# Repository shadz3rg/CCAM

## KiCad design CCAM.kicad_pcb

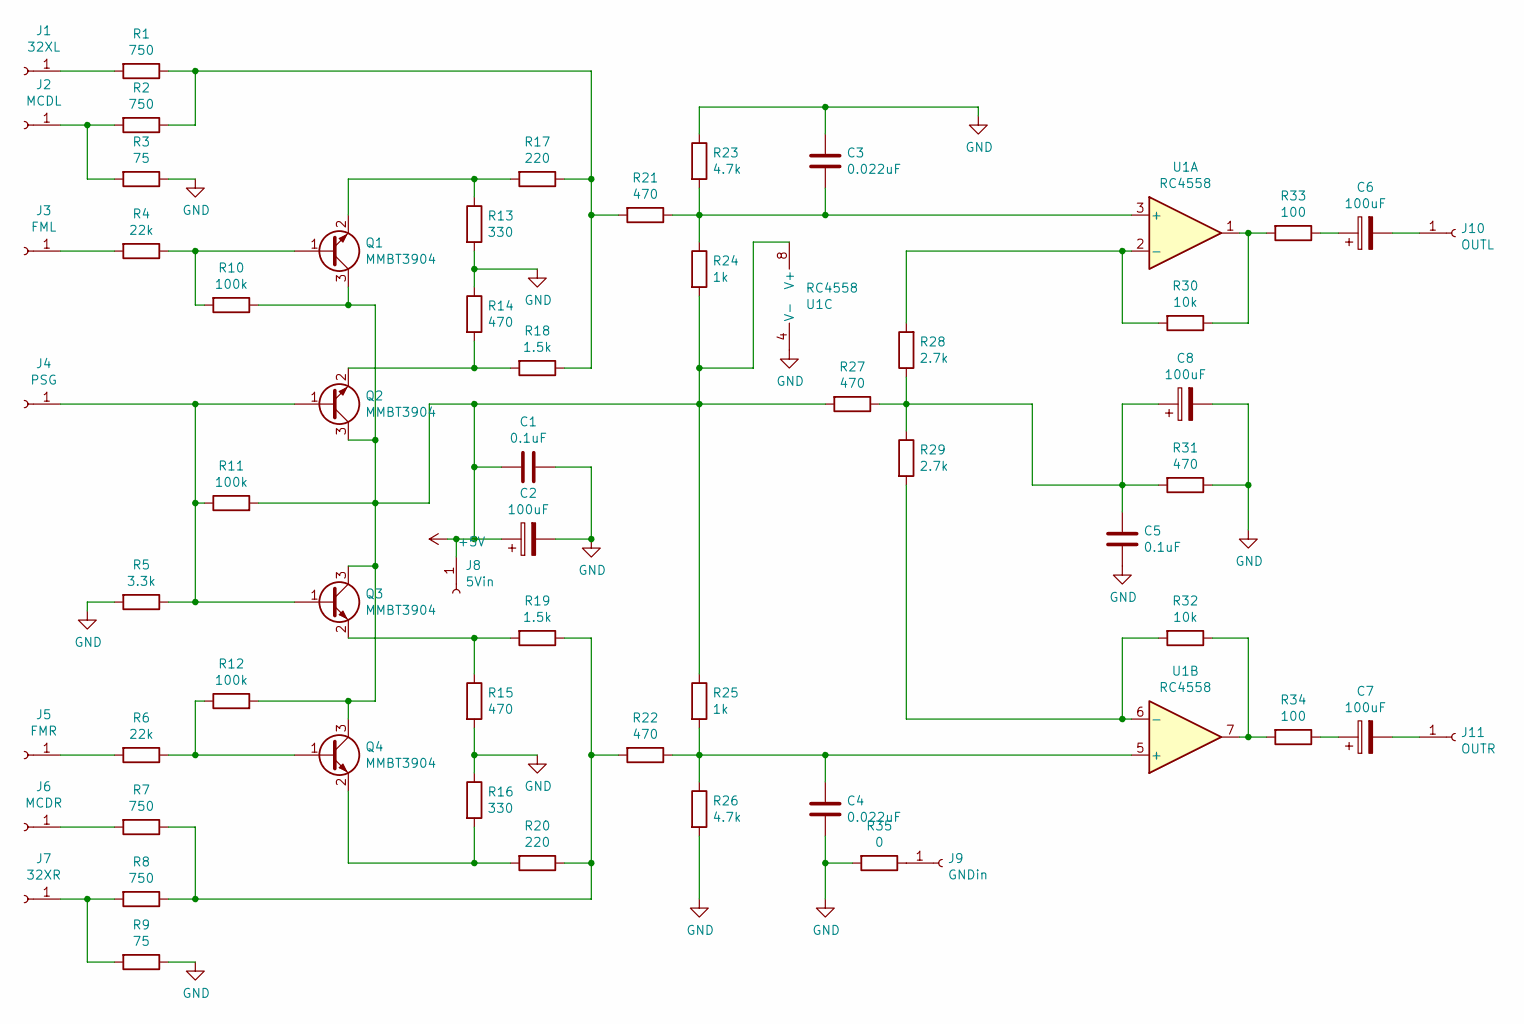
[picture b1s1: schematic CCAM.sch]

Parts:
C1, C5: 0.1uF; C_1210_3225Metric
C2, C6, C7, C8: 100uF; CP_EIA-3528-12_Kemet-T
C3, C4: 0.022uF; C_1210_3225Metric
J1: 32XL; SolderWirePad_1x01_SMD_1x2mm
J2: MCDL; SolderWirePad_1x01_SMD_1x2mm
J3: FML; SolderWirePad_1x01_SMD_1x2mm
J4: PSG; SolderWirePad_1x01_SMD_1x2mm
J5: FMR; SolderWirePad_1x01_SMD_1x2mm
J6: MCDR; SolderWirePad_1x01_SMD_1x2mm
J7: 32XR; SolderWirePad_1x01_SMD_1x2mm
J8: 5Vin; SolderWirePad_1x01_SMD_1x2mm
J9: GNDin; SolderWirePad_1x01_SMD_1x2mm
J10: OUTL; SolderWirePad_1x01_SMD_1x2mm
J11: OUTR; SolderWirePad_1x01_SMD_1x2mm
Q1, Q2, Q3, Q4: MMBT3904; SOT-23
R1, R2, R7, R8: 750; R_1206_3216Metric
R3, R9: 75; R_1206_3216Metric
R4, R6: 22k; R_1206_3216Metric
R5: 3.3k; R_1206_3216Metric
R10, R11, R12: 100k; R_1206_3216Metric
R13, R16: 330; R_1206_3216Metric
R14, R15, R21, R22, R27, R31: 470; R_1206_3216Metric
R17, R20: 220; R_1206_3216Metric
R18, R19: 1.5k; R_1206_3216Metric
R23, R26: 4.7k; R_1206_3216Metric
R24, R25: 1k; R_1206_3216Metric
R28, R29: 2.7k; R_1206_3216Metric
R30, R32: 10k; R_1206_3216Metric
R33, R34: 100; R_1206_3216Metric
R35: 0; R_1206_3216Metric
U1: RC4558; SOIC-8_3.9x4.9mm_P1.27mm

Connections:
+5V: C1.2, C2.1, J8.1, Q1.3 (C), Q2.3 (C), Q3.3 (C), Q4.3 (C), R10.1, R11.2, R12.2, R24.2, R25.1, R27.2, U1.8 (V+)
GND: C1.1, C2.2, C3.1, C4.2, C5.2, C8.2, R3.1, R5.2, R9.1, R13.2, R14.1, R15.2, R16.1, R23.1, R26.2, R31.1, R35.2, U1.4 (V-)
unnamed: C3.2, R21.1, R23.2, R24.1, U1.3 (+)
unnamed: C4.1, R22.1, R25.2, R26.1, U1.5 (+)
unnamed: C5.1, C8.1, R27.1, R28.1, R29.1, R31.2
unnamed: C6.1, R33.1
unnamed: C6.2, J10.1
unnamed: C7.1, R34.1
unnamed: C7.2, J11.1
unnamed: J1.1, R1.2
unnamed: J2.1, R2.2, R3.2
unnamed: J3.1, R4.2
unnamed: J4.1, Q2.1 (B), Q3.1 (B), R5.1, R11.1
unnamed: J5.1, R6.2
unnamed: J6.1, R7.2
unnamed: J7.1, R8.2, R9.2
unnamed: J9.1, R35.1
unnamed: Q1.1 (B), R4.1, R10.2
unnamed: Q1.2 (E), R13.1, R17.2
unnamed: Q2.2 (E), R14.2, R18.2
unnamed: Q3.2 (E), R15.1, R19.2
unnamed: Q4.1 (B), R6.1, R12.1
unnamed: Q4.2 (E), R16.2, R20.2
unnamed: R1.1, R2.1, R17.1, R18.1, R21.2
unnamed: R7.1, R8.1, R19.1, R20.1, R22.2
unnamed: R28.2, R30.2, U1.2 (-)
unnamed: R29.2, R32.2, U1.6 (-)
unnamed: R30.1, R33.2, U1.1
unnamed: R32.1, R34.2, U1.7

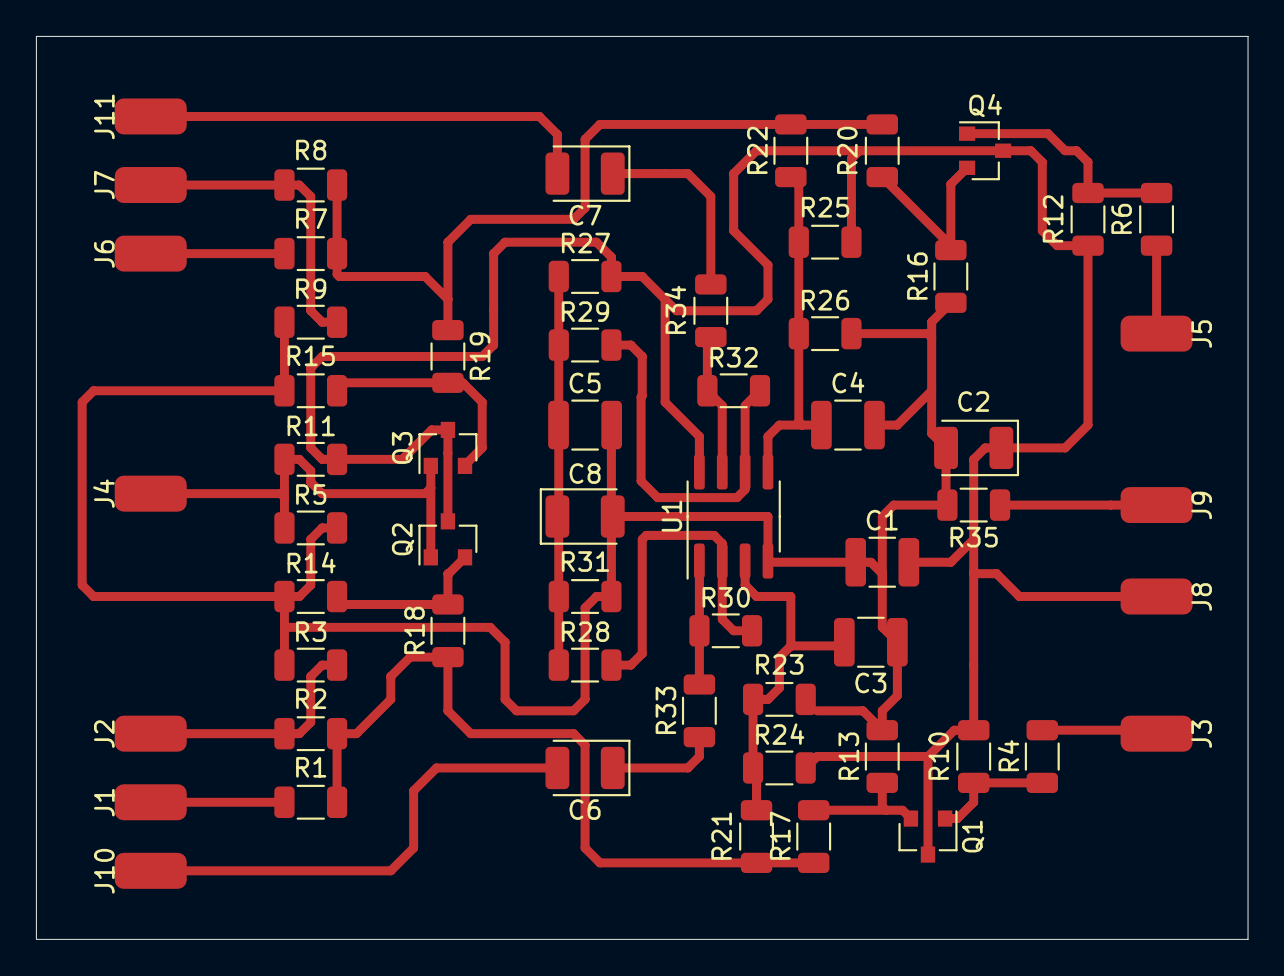
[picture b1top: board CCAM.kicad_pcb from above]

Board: 2 copper layers, 67.3 x 50.2 mm, 59 parts (0 on the bottom side), 29 nets.

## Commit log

2021-11-02 init
2021-11-03 Completed layout
2021-11-03 Trim layout
2021-11-04 Board optimization
